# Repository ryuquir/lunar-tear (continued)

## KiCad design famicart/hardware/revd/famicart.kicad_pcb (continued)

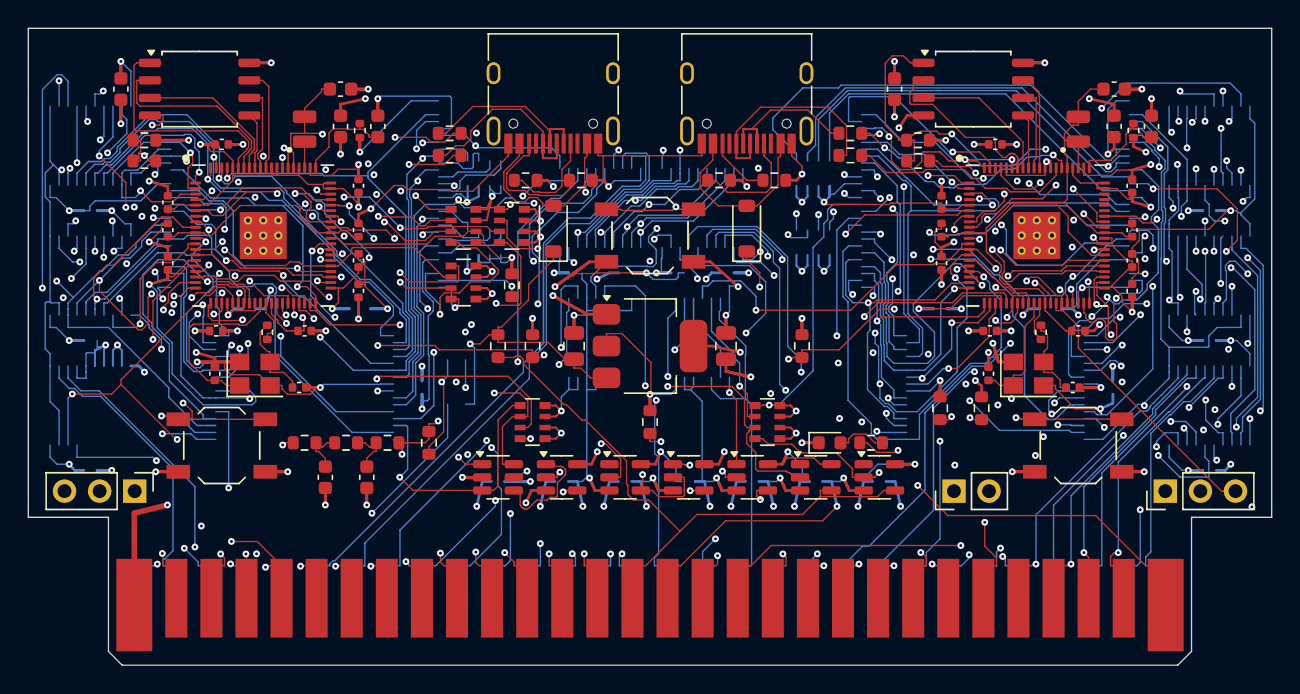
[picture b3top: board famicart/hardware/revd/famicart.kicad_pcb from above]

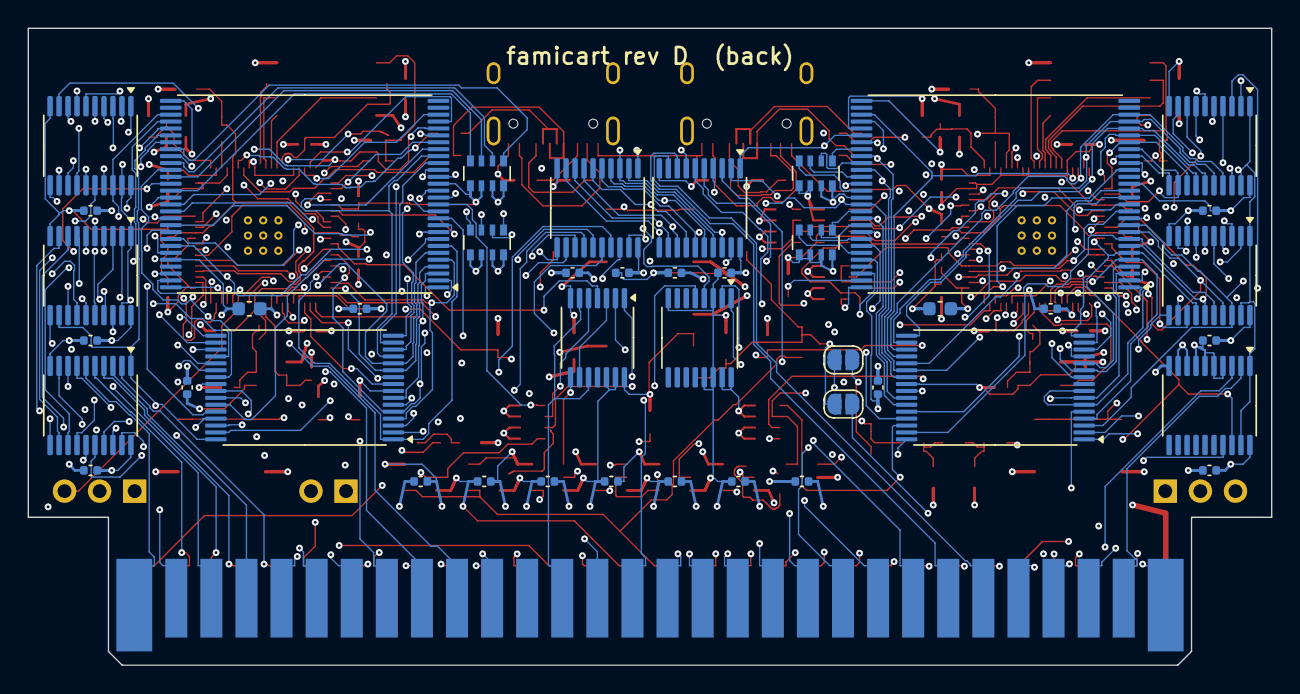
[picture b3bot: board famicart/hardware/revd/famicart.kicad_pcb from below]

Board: 6 copper layers, 90.0 x 46.1 mm, 140 parts (43 on the bottom side), 228 nets.

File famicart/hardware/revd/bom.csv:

Qty,Value,Footprint,References,Suggested part
1,Famicom 60-pin edge,Famicom_CardEdge_60,J1,"PCB card edge (gold fingers), no part"
2,RP2350B,QFN-80-1EP_10x10mm_P0.4mm_EP3.4x3.4mm,U1 U2,
2,W25Q16JVSSIQ,SOIC-8_5.23x5.23mm_P1.27mm,U3 U4,
2,100n,C_0603_1608Metric,C1 C17,X7R 0603 16V
9,10k,R_0603_1608Metric,R1 R7 R17 R22 R23 R24 R25 R26 R27,0603 1%
4,1k,R_0603_1608Metric,R2 R8 R21 R28,0603 1%
2,12MHz ABM8-272-T3,Crystal_SMD_3225-4Pin_3.2x2.5mm,Y1 Y2,
2,1k,R_0402_1005Metric,R3 R9,0603 1%
4,15p,C_0402_1005Metric,C2 C3 C18 C19,
2,3.3uH AOTA-B201610S3R3,L_0806_2016Metric,L1 L2,
6,4.7u,C_0603_1608Metric,C4 C5 C6 C20 C21 C22,
2,33,R_0402_1005Metric,R4 R10,
4,27,R_0603_1608Metric,R5 R6 R11 R12,
41,100n,C_0402_1005Metric,C7 C8 C9 C10 C11 C12 C13 C14 C15 C16 C23 C24 C25 C26 C27 C28 C29 C30 C31 C32 C37 C39 C41 C42 C43 C44 C45 C46 C47 C48 C49 C50 C51 C52 C53 C54 C55 C56 C57 C58 C59,X7R 0603 16V
1,USB-C PRG/mapper,USB_C_Receptacle_HRO_TYPE-C-31-M-12,J3,
4,5.1k,R_0603_1608Metric,R13 R14 R15 R16,0603 1% (USB-C CC pull-down)
1,USB-C CHR,USB_C_Receptacle_HRO_TYPE-C-31-M-12,J4,
2,B5819W,D_SOD-123,D1 D2,
1,RESET,SW_SPST_TL3342,SW1,E-Switch TL3342 / any 4.7x3.5 mm low-profile tactile
1,BOOTSEL A,SW_SPST_TL3342,SW2,
1,BOOTSEL B,SW_SPST_TL3342,SW3,
1,RUN/GND,PinHeader_1x02_P2.54mm_Vertical,J2,"2-pin 2.54 mm header (optional, wire to the console reset switch)"
1,SWD A,PinHeader_1x03_P2.54mm_Vertical,J5,
1,SWD B,PinHeader_1x03_P2.54mm_Vertical,J6,
1,AMS1117-3.3,SOT-223-3_TabPin2,U28,
2,10u,C_0805_2012Metric,C33 C34,X5R 0805 10V
2,2.2k,R_0603_1608Metric,R18 R19,0603 1%
1,4.7k,R_0603_1608Metric,R20,0603 1%
2,10n,C_0603_1608Metric,C35 C36,X7R 0603 50V
1,AUDIO bypass,SolderJumper-2_P1.3mm_Open_RoundedPad1.0x1.5mm,JP1,
1,CART_PRESENT,SolderJumper-2_P1.3mm_Open_RoundedPad1.0x1.5mm,JP2,
9,10k x4,R_Array_Convex_4x0603,RN1 RN2 RN3 RN4 RN5 RN6 RN7 RN8 RN9,
2,S29GL01GS 1Gbit NOR,TSOP-I-56_18.4x14mm_P0.5mm,U5 U6,
2,1u,C_0603_1608Metric,C38 C40,
1,FM28V100 128Kx8 F-RAM,TSOP-I-32_11.8x8mm_P0.5mm,U7,
1,IS62WV5128 512Kx8 SRAM,TSOP-I-32_11.8x8mm_P0.5mm,U8,
1,74LVC541 U9,TSSOP-20_4.4x6.5mm_P0.65mm,U9,
1,74LVC541 U10,TSSOP-20_4.4x6.5mm_P0.65mm,U10,
1,74LVC541 U11,TSSOP-20_4.4x6.5mm_P0.65mm,U11,
1,74LVC245 CPU data,TSSOP-20_4.4x6.5mm_P0.65mm,U12,
1,74LVC245 CPU->PPU data bridge,TSSOP-20_4.4x6.5mm_P0.65mm,U24,
1,74LVC139 CHR ROM/RAM select,TSSOP-16_4.4x5mm_P0.65mm,U22,
1,74LVC541 U17,TSSOP-20_4.4x6.5mm_P0.65mm,U17,
1,74LVC541 U18,TSSOP-20_4.4x6.5mm_P0.65mm,U18,
1,74LVC245 PPU data,TSSOP-20_4.4x6.5mm_P0.65mm,U19,
1,74LVC00 PPU access / CIRAM glue,TSSOP-14_4.4x5mm_P0.65mm,U20,
1,74LVC1G11 AND3: CPU data enable,SOT-23-6,U13,
1,74LVC1G32 OR: CPU 245 /OE,SOT-23-5,U14,
1,74LVC1G04 INV: R/W,SOT-23-5,U15,
1,74LVC1G00 NAND: WRAM /WE,SOT-23-5,U16,
1,74LVC1G32 OR: PPU 245 /OE,SOT-23-5,U21,
1,74LVC1G07 OD: /IRQ A,SOT-23-5,U26,
1,74LVC1G07 OD: /IRQ B,SOT-23-5,U27,
1,green 0603,LED_0603_1608Metric,D3,

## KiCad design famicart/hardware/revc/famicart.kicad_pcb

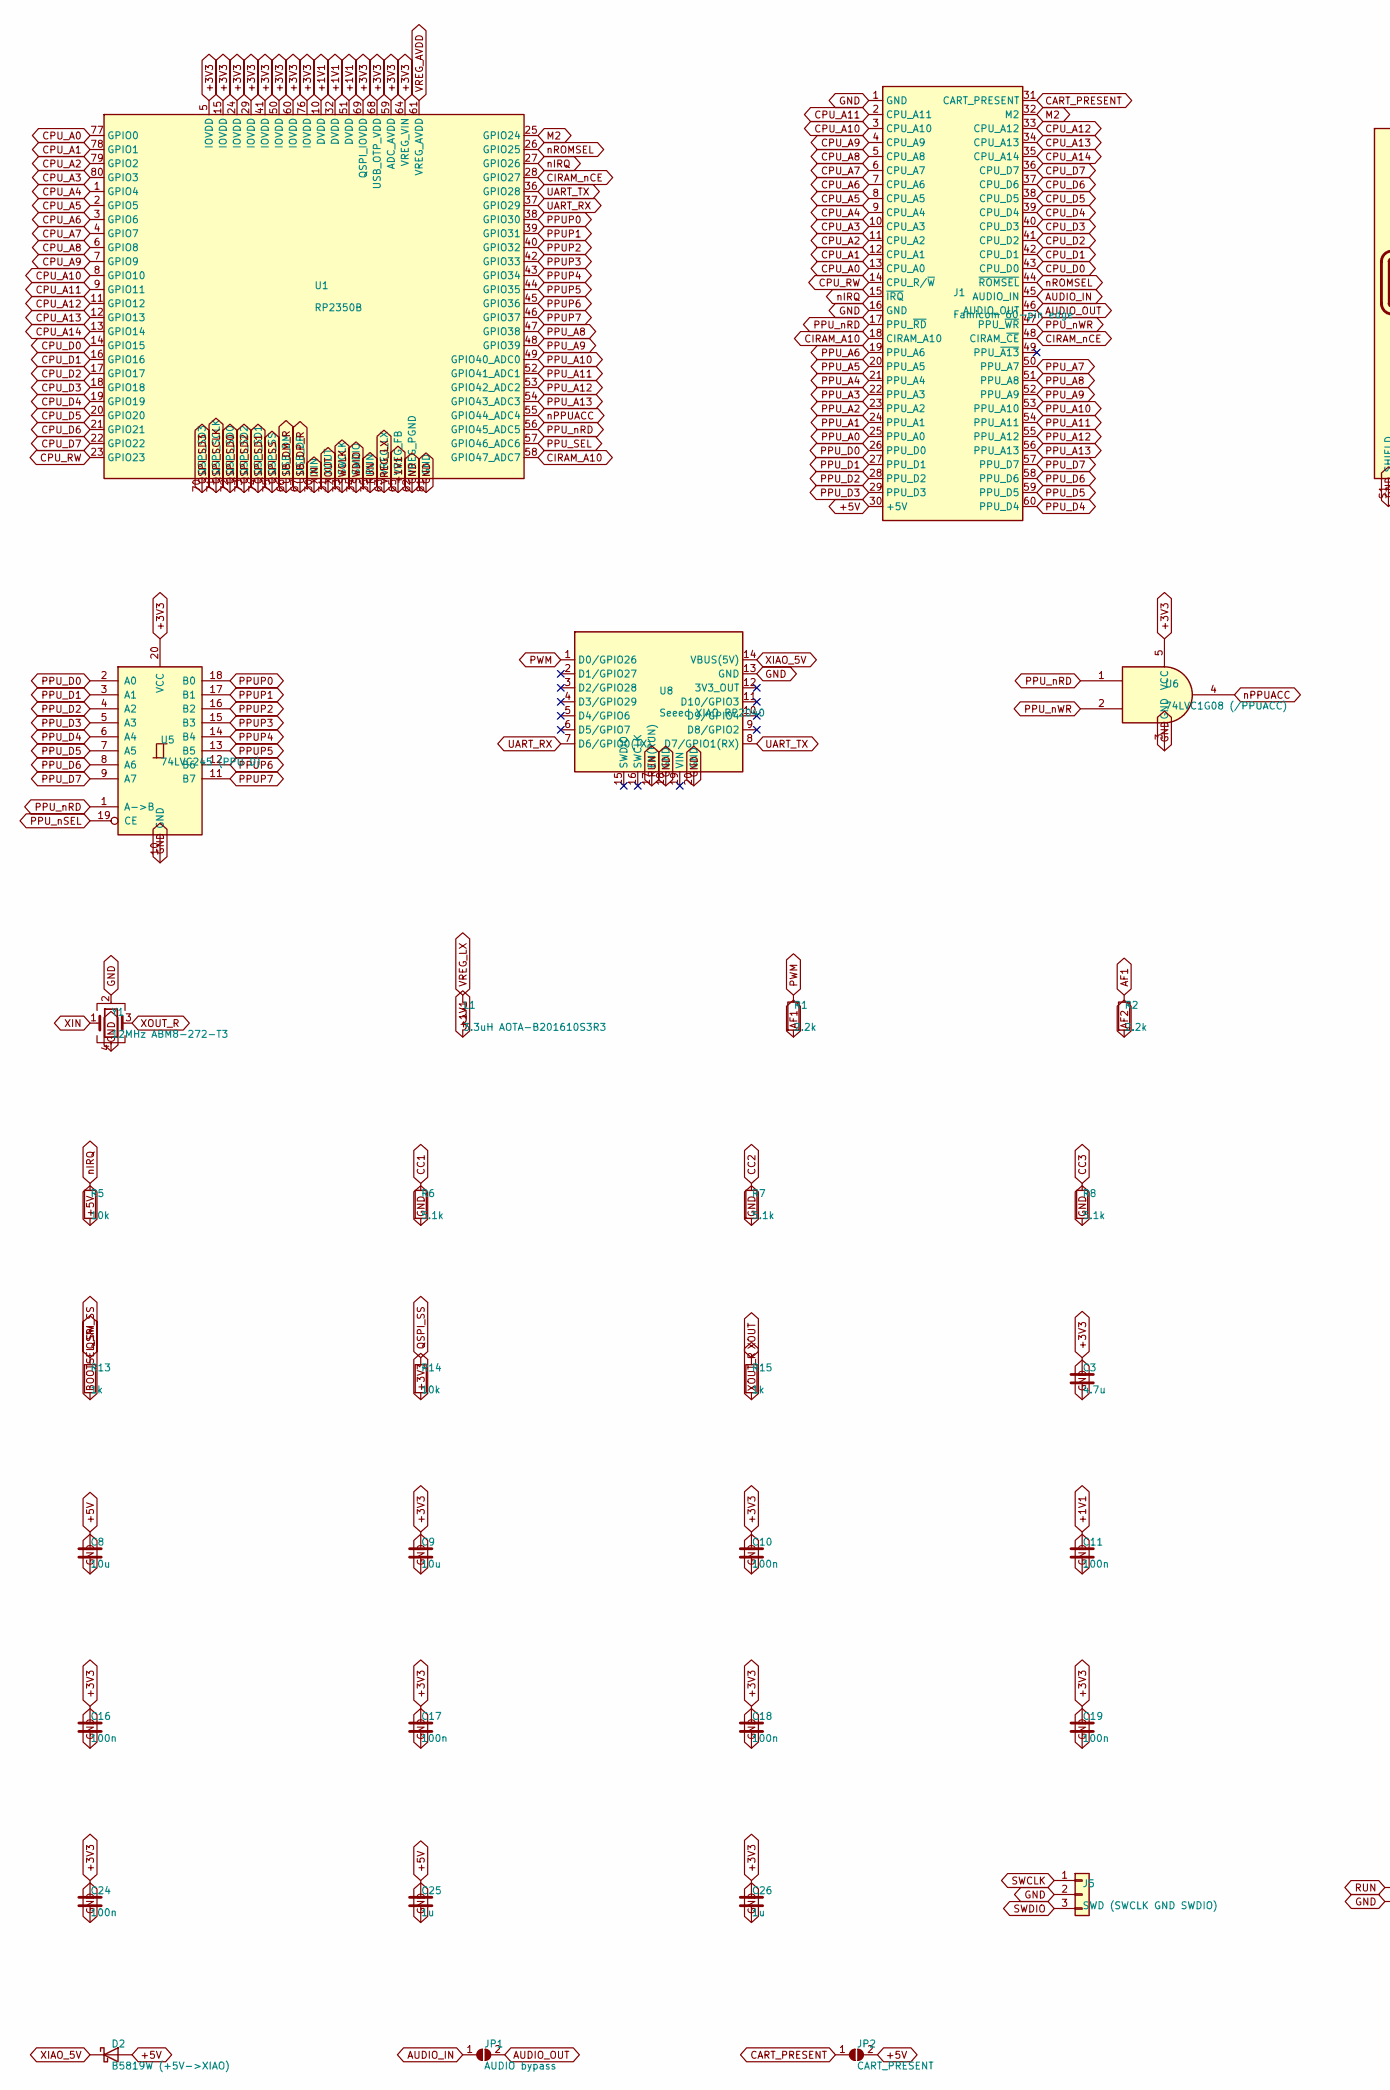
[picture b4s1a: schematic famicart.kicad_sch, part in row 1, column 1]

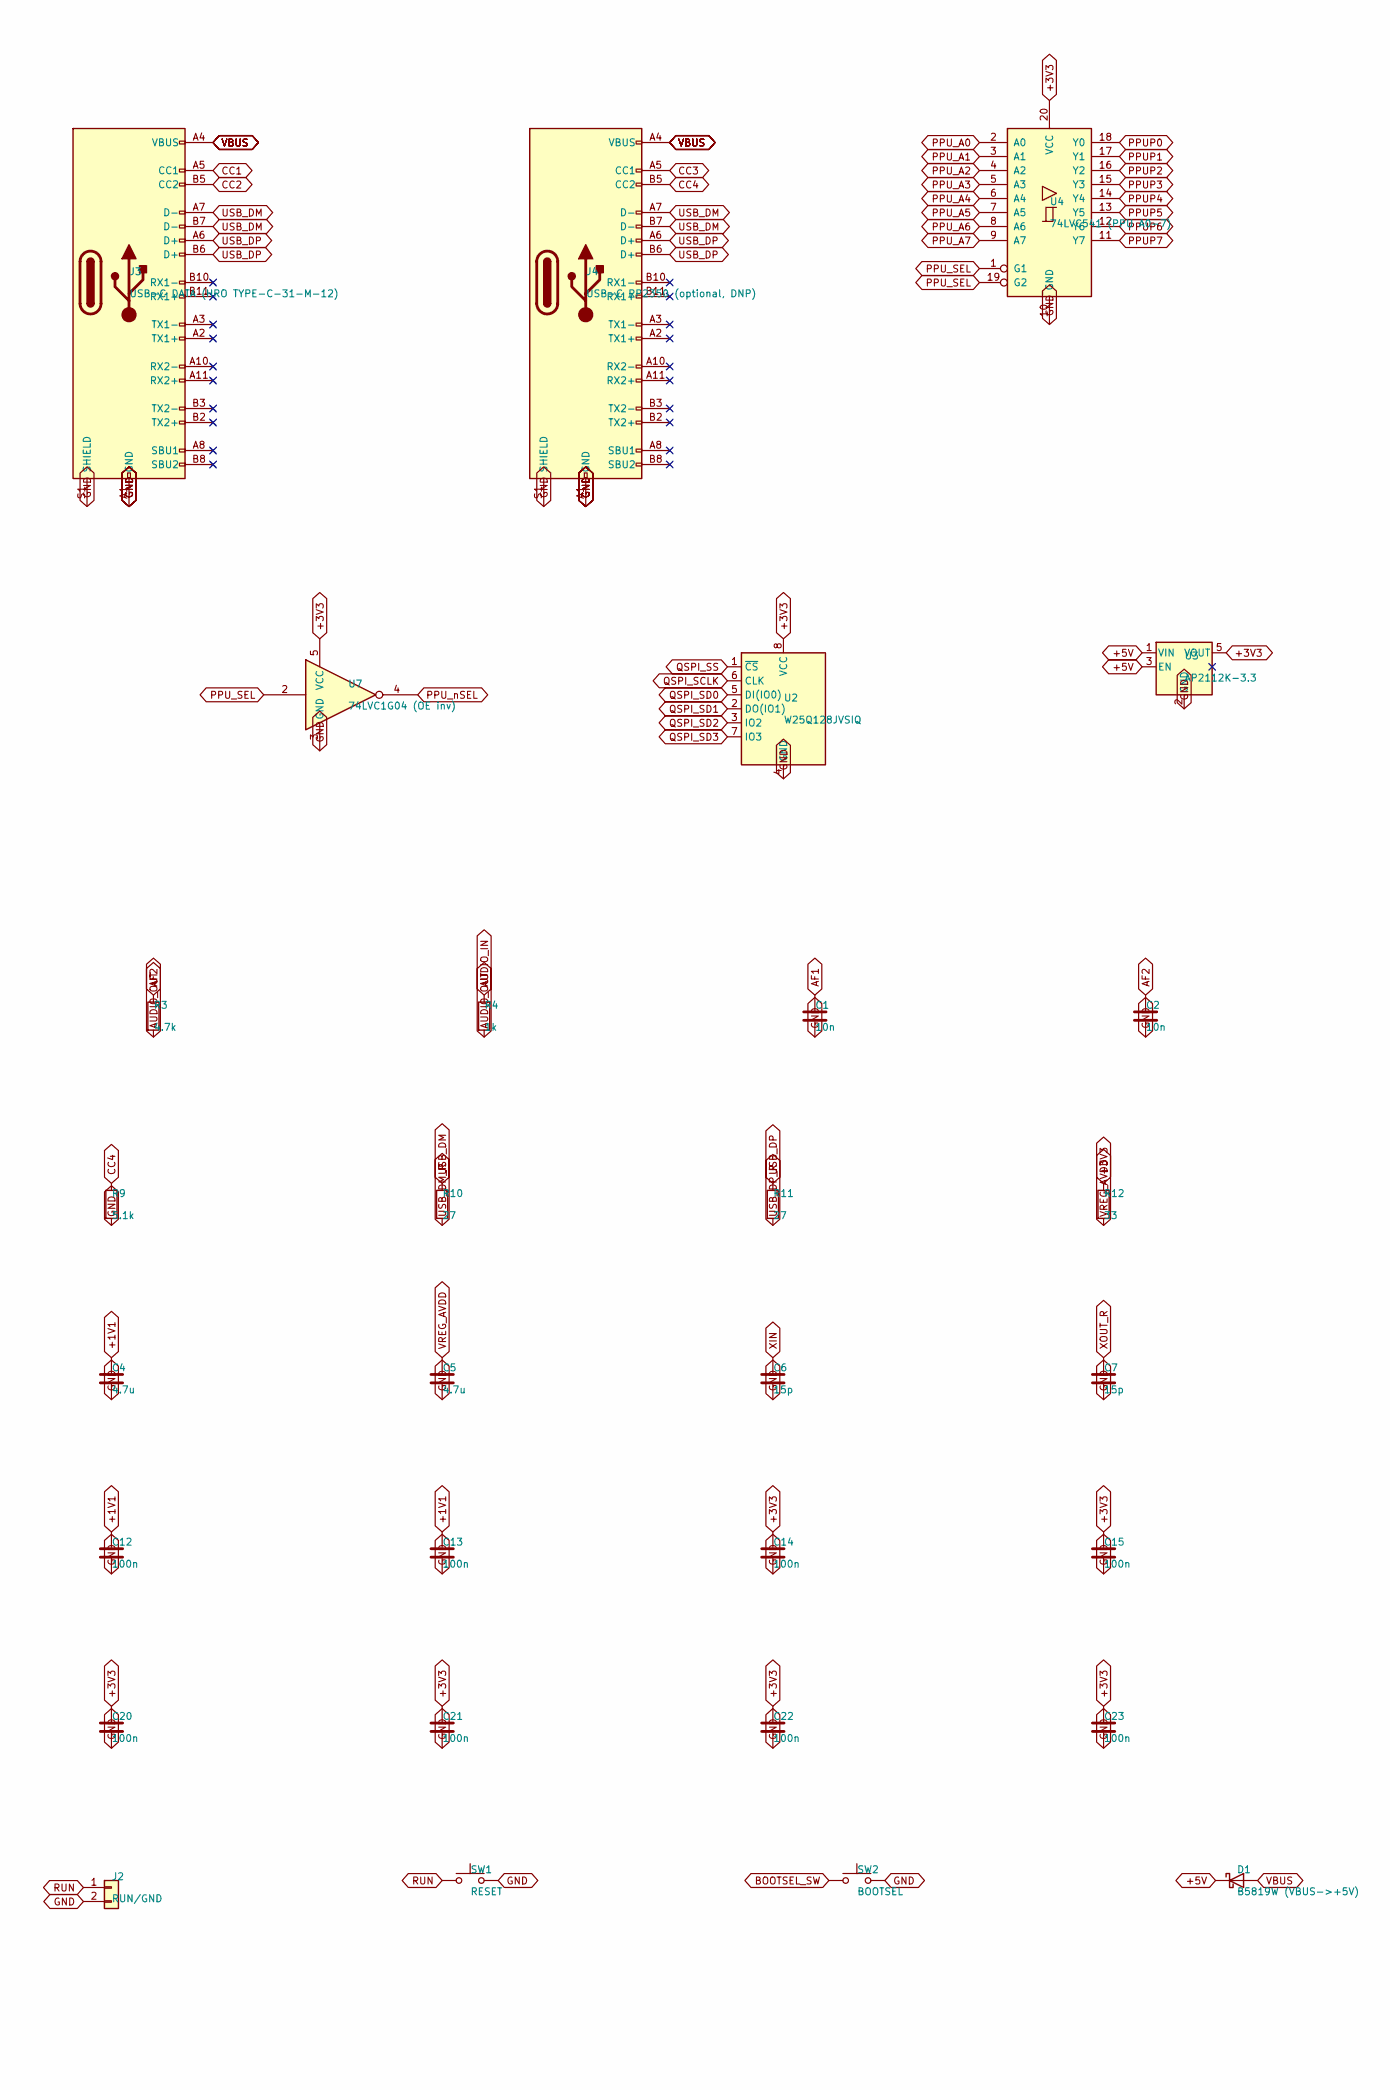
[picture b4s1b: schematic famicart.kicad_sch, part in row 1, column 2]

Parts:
C1, C2: 10n; C_0603_1608Metric
C3, C4, C5: 4.7u; C_0603_1608Metric
C6, C7: 15p; C_0402_1005Metric
C8, C9: 10u; C_0805_2012Metric
C10, C21, C22, C23, C24: 100n; C_0603_1608Metric
C11, C12, C13, C14, C15, C16, C17, C18, C19, C20: 100n; C_0402_1005Metric
C25, C26: 1u; C_0603_1608Metric
D1: B5819W (VBUS->+5V); D_SOD-123
D2: B5819W (+5V->XIAO); D_SOD-123
J1: Famicom 60-pin edge; Famicom_CardEdge_60
J2: RUN/GND; PinHeader_1x02_P2.54mm_Vertical
J3: USB-C DATA (HRO TYPE-C-31-M-12); USB_C_Receptacle_HRO_TYPE-C-31-M-12
J4: USB-C RP2350 (optional, DNP); USB_C_Receptacle_HRO_TYPE-C-31-M-12
J5: SWD (SWCLK GND SWDIO); PinHeader_1x03_P2.54mm_Vertical
JP1: AUDIO bypass; SolderJumper-2_P1.3mm_Open_RoundedPad1.0x1.5mm
JP2: CART_PRESENT; SolderJumper-2_P1.3mm_Open_RoundedPad1.0x1.5mm
L1: 3.3uH AOTA-B201610S3R3; L_0806_2016Metric
R1, R2: 2.2k; R_0603_1608Metric
R3: 4.7k; R_0603_1608Metric
R4, R13: 1k; R_0603_1608Metric
R5, R14: 10k; R_0603_1608Metric
R6, R7, R8, R9: 5.1k; R_0603_1608Metric
R10, R11: 27; R_0603_1608Metric
R12: 33; R_0402_1005Metric
R15: 1k; R_0402_1005Metric
SW1: RESET; SW_SPST_TL3342
SW2: BOOTSEL; SW_SPST_TL3342
U1: RP2350B; QFN-80-1EP_10x10mm_P0.4mm_EP3.4x3.4mm
U2: W25Q128JVSIQ; SOIC-8_5.23x5.23mm_P1.27mm
U3: AP2112K-3.3; SOT-23-5
U4: 74LVC541 (PPU A0-7); TSSOP-20_4.4x6.5mm_P0.65mm
U5: 74LVC245 (PPU D); TSSOP-20_4.4x6.5mm_P0.65mm
U6: 74LVC1G08 (/PPUACC); SOT-23-5
U7: 74LVC1G04 (OE inv); SOT-23-5
U8: Seeed XIAO RP2040; XIAO-RP2040-SMD
Y1: 12MHz ABM8-272-T3; Crystal_SMD_3225-4Pin_3.2x2.5mm

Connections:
+1V1: C4.1, C11.1, C12.1, C13.1, L1.2, U1.10 (DVDD), U1.32 (DVDD), U1.51 (DVDD), U1.65 (VREG_FB)
+3V3: C3.1, C9.1, C10.1, C14.1, C15.1, C16.1, C17.1, C18.1, C19.1, C20.1, C21.1, C22.1, C23.1, C24.1, C26.1, R12.1, R14.2, U1.5 (IOVDD), U1.15 (IOVDD), U1.24 (IOVDD), U1.29 (IOVDD), U1.41 (IOVDD), U1.50 (IOVDD), U1.59 (ADC_AVDD), U1.60 (IOVDD), U1.64 (VREG_VIN), U1.68 (USB_OTP_VDD), U1.69 (QSPI_IOVDD), U1.76 (IOVDD), U2.8 (VCC), U3.5 (VOUT), U4.20 (VCC), U5.20 (VCC), U6.5 (VCC), U7.5 (VCC)
+5V: C8.1, C25.1, D1.1 (K), D2.2 (A), J1.30 (+5V), JP2.2 (B), R5.2, U3.1 (VIN), U3.3 (EN)
AF1: C1.1, R1.2, R2.1
AF2: C2.1, R2.2, R3.1
AUDIO_IN: J1.45 (AUDIO_IN), JP1.1 (A), R4.1
AUDIO_OUT: J1.46 (AUDIO_OUT), JP1.2 (B), R3.2, R4.2
BOOTSEL_SW: R13.2, SW2.1
CART_PRESENT: J1.31 (CART_PRESENT), JP2.1 (A)
CC1: J3.A5 (CC1), R6.1
CC2: J3.B5 (CC2), R7.1
CC3: J4.A5 (CC1), R8.1
CC4: J4.B5 (CC2), R9.1
CIRAM_A10: J1.18 (CIRAM_A10), U1.58 (GPIO47_ADC7)
CIRAM_nCE: J1.48 (CIRAM_~CE), U1.28 (GPIO27)
CPU_A0: J1.13 (CPU_A0), U1.77 (GPIO0)
CPU_A1: J1.12 (CPU_A1), U1.78 (GPIO1)
CPU_A2: J1.11 (CPU_A2), U1.79 (GPIO2)
CPU_A3: J1.10 (CPU_A3), U1.80 (GPIO3)
CPU_A4: J1.9 (CPU_A4), U1.1 (GPIO4)
CPU_A5: J1.8 (CPU_A5), U1.2 (GPIO5)
CPU_A6: J1.7 (CPU_A6), U1.3 (GPIO6)
CPU_A7: J1.6 (CPU_A7), U1.4 (GPIO7)
CPU_A8: J1.5 (CPU_A8), U1.6 (GPIO8)
CPU_A9: J1.4 (CPU_A9), U1.7 (GPIO9)
CPU_A10: J1.3 (CPU_A10), U1.8 (GPIO10)
CPU_A11: J1.2 (CPU_A11), U1.9 (GPIO11)
CPU_A12: J1.33 (CPU_A12), U1.11 (GPIO12)
CPU_A13: J1.34 (CPU_A13), U1.12 (GPIO13)
CPU_A14: J1.35 (CPU_A14), U1.13 (GPIO14)
CPU_D0: J1.43 (CPU_D0), U1.14 (GPIO15)
CPU_D1: J1.42 (CPU_D1), U1.16 (GPIO16)
CPU_D2: J1.41 (CPU_D2), U1.17 (GPIO17)
CPU_D3: J1.40 (CPU_D3), U1.18 (GPIO18)
CPU_D4: J1.39 (CPU_D4), U1.19 (GPIO19)
CPU_D5: J1.38 (CPU_D5), U1.20 (GPIO20)
CPU_D6: J1.37 (CPU_D6), U1.21 (GPIO21)
CPU_D7: J1.36 (CPU_D7), U1.22 (GPIO22)
CPU_RW: J1.14 (CPU_R/~W), U1.23 (GPIO23)
GND: C1.2, C2.2, C3.2, C4.2, C5.2, C6.2, C7.2, C8.2, C9.2, C10.2, C11.2, C12.2, C13.2, C14.2, C15.2, C16.2, C17.2, C18.2, C19.2, C20.2, C21.2, C22.2, C23.2, C24.2, C25.2, C26.2, J1.1 (GND), J1.16 (GND), J2.2, J3.A1 (GND), J3.A12 (GND), J3.B1 (GND), J3.B12 (GND), J3.S1 (SHIELD), J4.A1 (GND), J4.A12 (GND), J4.B1 (GND), J4.B12 (GND), J4.S1 (SHIELD), J5.2, R6.2, R7.2, R8.2, R9.2, SW1.2, SW2.2, U1.62 (VREG_PGND), U1.81 (GND), U2.4 (GND), U3.2 (GND), U4.10 (GND), U5.10 (GND), U6.3 (GND), U7.3 (GND), U8.13 (GND), U8.18 (GND), U8.20 (GND), Y1.2, Y1.4
M2: J1.32 (M2), U1.25 (GPIO24)
PPUP0: U1.38 (GPIO30), U4.18 (Y0), U5.18 (B0)
PPUP1: U1.39 (GPIO31), U4.17 (Y1), U5.17 (B1)
PPUP2: U1.40 (GPIO32), U4.16 (Y2), U5.16 (B2)
PPUP3: U1.42 (GPIO33), U4.15 (Y3), U5.15 (B3)
PPUP4: U1.43 (GPIO34), U4.14 (Y4), U5.14 (B4)
PPUP5: U1.44 (GPIO35), U4.13 (Y5), U5.13 (B5)
PPUP6: U1.45 (GPIO36), U4.12 (Y6), U5.12 (B6)
PPUP7: U1.46 (GPIO37), U4.11 (Y7), U5.11 (B7)
PPU_A0: J1.25 (PPU_A0), U4.2 (A0)
PPU_A1: J1.24 (PPU_A1), U4.3 (A1)
PPU_A2: J1.23 (PPU_A2), U4.4 (A2)
PPU_A3: J1.22 (PPU_A3), U4.5 (A3)
PPU_A4: J1.21 (PPU_A4), U4.6 (A4)
PPU_A5: J1.20 (PPU_A5), U4.7 (A5)
PPU_A6: J1.19 (PPU_A6), U4.8 (A6)
PPU_A7: J1.50 (PPU_A7), U4.9 (A7)
PPU_A8: J1.51 (PPU_A8), U1.47 (GPIO38)
PPU_A9: J1.52 (PPU_A9), U1.48 (GPIO39)
PPU_A10: J1.53 (PPU_A10), U1.49 (GPIO40_ADC0)
PPU_A11: J1.54 (PPU_A11), U1.52 (GPIO41_ADC1)
PPU_A12: J1.55 (PPU_A12), U1.53 (GPIO42_ADC2)
PPU_A13: J1.56 (PPU_A13), U1.54 (GPIO43_ADC3)
PPU_D0: J1.26 (PPU_D0), U5.2 (A0)
PPU_D1: J1.27 (PPU_D1), U5.3 (A1)
PPU_D2: J1.28 (PPU_D2), U5.4 (A2)
PPU_D3: J1.29 (PPU_D3), U5.5 (A3)
PPU_D4: J1.60 (PPU_D4), U5.6 (A4)
PPU_D5: J1.59 (PPU_D5), U5.7 (A5)
PPU_D6: J1.58 (PPU_D6), U5.8 (A6)
PPU_D7: J1.57 (PPU_D7), U5.9 (A7)
PPU_SEL: U1.57 (GPIO46_ADC6), U4.1 (G1), U4.19 (G2), U7.2
PPU_nRD: J1.17 (PPU_~RD), U1.56 (GPIO45_ADC5), U5.1 (A->B), U6.1
PPU_nSEL: U5.19 (CE), U7.4
PPU_nWR: J1.47 (PPU_~WR), U6.2
PWM: R1.1, U8.1 (D0/GPIO26)
QSPI_SCLK: U1.71 (QSPI_SCLK), U2.6 (CLK)
QSPI_SD0: U1.72 (QSPI_SD0), U2.5 (DI(IO0))
QSPI_SD1: U1.74 (QSPI_SD1), U2.2 (DO(IO1))
QSPI_SD2: U1.73 (QSPI_SD2), U2.3 (IO2)
QSPI_SD3: U1.70 (QSPI_SD3), U2.7 (IO3)
QSPI_SS: R13.1, R14.1, U1.75 (QSPI_SS), U2.1 (~CS)
RUN: J2.1, SW1.1, U1.35 (RUN), U8.17 (EN(RUN))
SWCLK: J5.1, U1.33 (SWCLK)
SWDIO: J5.3, U1.34 (SWDIO)
UART_RX: U1.37 (GPIO29), U8.7 (D6/GPIO0(TX))
UART_TX: U1.36 (GPIO28), U8.8 (D7/GPIO1(RX))
USB_DM: J3.A7 (D-), J3.B7 (D-), J4.A7 (D-), J4.B7 (D-), R10.1
USB_DM_R: R10.2, U1.66 (USB_DM)
USB_DP: J3.A6 (D+), J3.B6 (D+), J4.A6 (D+), J4.B6 (D+), R11.1
USB_DP_R: R11.2, U1.67 (USB_DP)
VBUS: D1.2 (A), J3.A4 (VBUS), J3.A9 (VBUS), J3.B4 (VBUS), J3.B9 (VBUS), J4.A4 (VBUS), J4.A9 (VBUS), J4.B4 (VBUS), J4.B9 (VBUS)
VREG_AVDD: C5.1, R12.2, U1.61 (VREG_AVDD)
VREG_LX: L1.1, U1.63 (VREG_LX)
XIAO_5V: D2.1 (K), U8.14 (VBUS(5V))
XIN: C6.1, U1.30 (XIN), Y1.1
XOUT: R15.1, U1.31 (XOUT)
XOUT_R: C7.1, R15.2, Y1.3
nIRQ: J1.15 (~IRQ), R5.1, U1.27 (GPIO26)
nPPUACC: U1.55 (GPIO44_ADC4), U6.4
nROMSEL: J1.44 (~ROMSEL), U1.26 (GPIO25)

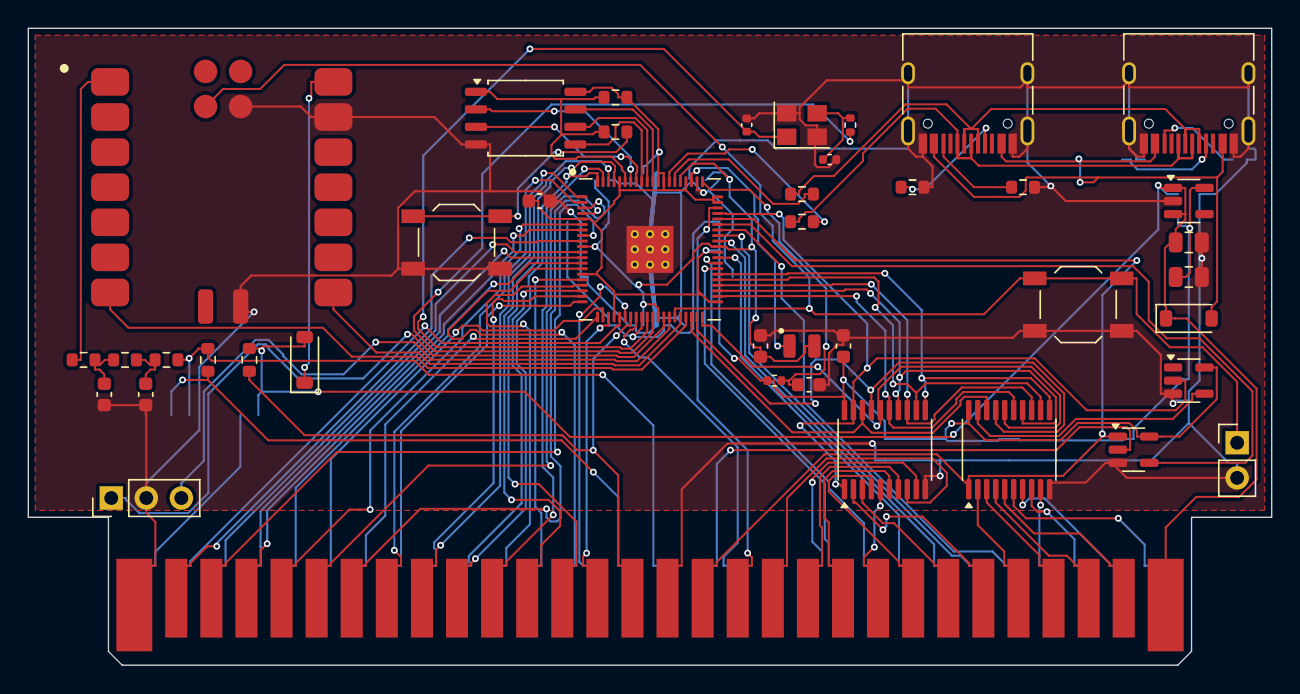
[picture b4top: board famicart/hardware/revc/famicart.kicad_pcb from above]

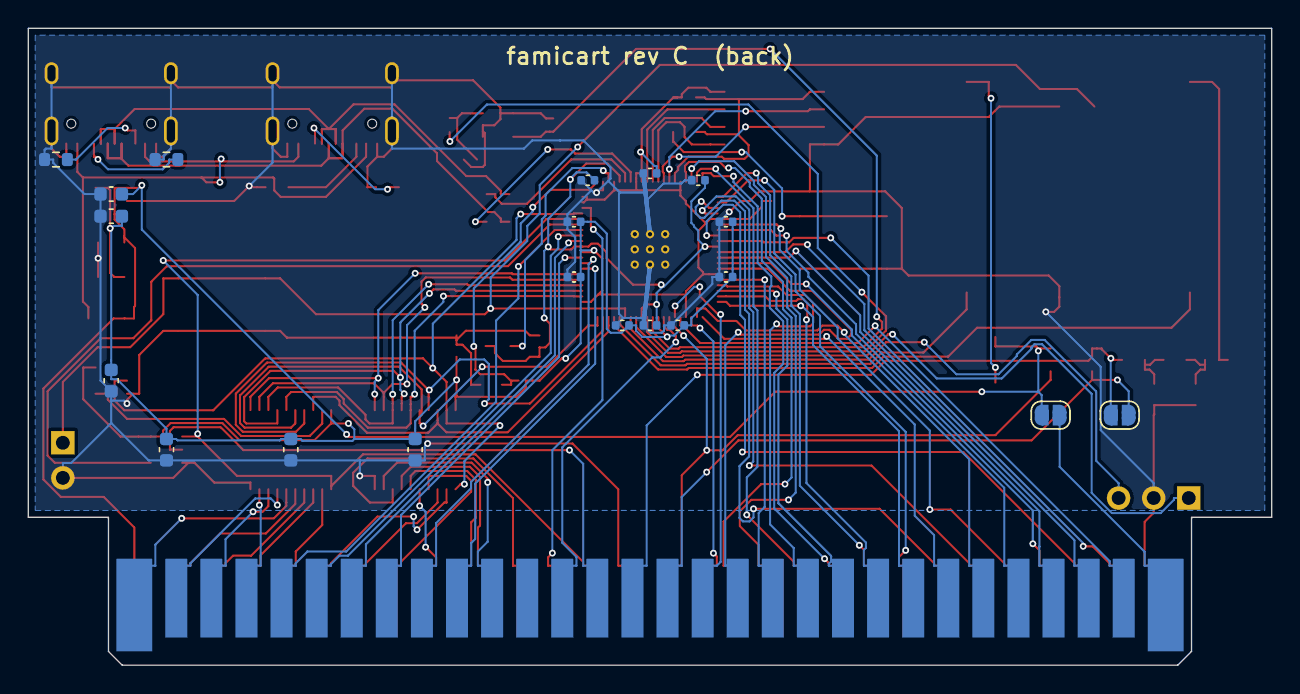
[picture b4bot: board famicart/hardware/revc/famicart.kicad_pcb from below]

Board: 2 copper layers, 90.0 x 46.1 mm, 62 parts (20 on the bottom side), 101 nets.

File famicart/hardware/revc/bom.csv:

Qty,Value,Footprint,References,Suggested part
1,Famicom 60-pin edge,Famicom_CardEdge_60,J1,"PCB card edge (gold fingers), no part"
1,RP2350B,QFN-80-1EP_10x10mm_P0.4mm_EP3.4x3.4mm,U1,
1,W25Q128JVSIQ,SOIC-8_5.23x5.23mm_P1.27mm,U2,
1,AP2112K-3.3,SOT-23-5,U3,
1,74LVC541,TSSOP-20_4.4x6.5mm_P0.65mm,U4,Nexperia 74LVC541APW (TSSOP-20)
1,74LVC245,TSSOP-20_4.4x6.5mm_P0.65mm,U5,Nexperia 74LVC245APW (TSSOP-20)
1,74LVC1G08,SOT-23-5,U6,Nexperia 74LVC1G08GW / TI SN74LVC1G08DBV
1,74LVC1G04,SOT-23-5,U7,
1,Seeed XIAO RP2040,XIAO-RP2040-SMD,U8,
1,12MHz ABM8-272-T3,Crystal_SMD_3225-4Pin_3.2x2.5mm,Y1,
1,3.3uH AOTA-B201610S3R3,L_0806_2016Metric,L1,
1,USB-C DATA,USB_C_Receptacle_HRO_TYPE-C-31-M-12,J3,
1,USB-C RP2350,USB_C_Receptacle_HRO_TYPE-C-31-M-12,J4,
1,RUN/GND,PinHeader_1x02_P2.54mm_Vertical,J2,"2-pin 2.54 mm header (optional, wire to the console reset switch)"
1,SWD,PinHeader_1x03_P2.54mm_Vertical,J5,
1,RESET,SW_SPST_TL3342,SW1,E-Switch TL3342 / any 4.7x3.5 mm low-profile tactile
1,BOOTSEL,SW_SPST_TL3342,SW2,
2,2.2k,R_0603_1608Metric,R1 R2,0603 1%
1,4.7k,R_0603_1608Metric,R3,0603 1%
2,1k,R_0603_1608Metric,R4 R13,0603 1%
2,10n,C_0603_1608Metric,C1 C2,X7R 0603 50V
2,10k,R_0603_1608Metric,R5 R14,0603 1%
4,5.1k,R_0603_1608Metric,R6 R7 R8 R9,0603 1% (USB-C CC pull-down)
2,27,R_0603_1608Metric,R10 R11,
1,33,R_0402_1005Metric,R12,
1,1k,R_0402_1005Metric,R15,0603 1%
3,4.7u,C_0603_1608Metric,C3 C4 C5,
2,15p,C_0402_1005Metric,C6 C7,
2,10u,C_0805_2012Metric,C8 C9,X5R 0805 10V
5,100n,C_0603_1608Metric,C10 C21 C22 C23 C24,X7R 0603 16V
2,B5819W,D_SOD-123,D1 D2,
1,AUDIO bypass,SolderJumper-2_P1.3mm_Open_RoundedPad1.0x1.5mm,JP1,
1,CART_PRESENT,SolderJumper-2_P1.3mm_Open_RoundedPad1.0x1.5mm,JP2,
10,100n,C_0402_1005Metric,C11 C12 C13 C14 C15 C16 C17 C18 C19 C20,X7R 0603 16V
2,1u,C_0603_1608Metric,C25 C26,
